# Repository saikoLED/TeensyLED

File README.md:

TeensyLED Controller
====================
Copyright Brian Neltner 2015<br/>
Version 0.4 - May 21, 2015

Summary
-------
This provides a basic library and example code for interacting
with a RGBW LED light using Hue, Saturation, and Intensity (HSI)
mode. Also provided are a basic USB interface example, and an example
for using the fully isolated DMX interface.

CircuitHub design created for this board with pre-identified working
parts. Licensed under CERN Open Hardware license (http://www.ohwr.org/projects/cernohl) which
allows for anyone to copy, modify and distribute this design (and products manufactured therefrom) so long
as they are licensed under identical terms & maintain all copyrights.

https://circuithub.com/projects/neltnerb/TeensyLED

Software Features
-----------------
- HSI to RGBW library for interacting with LED sources with color correction.
- PID based fader that follows a random walk through colorspace.
- Tested basic DMX receiving software (just prints DMX data to USB Serial port for now).
- Basic debug example to set the brightness from the USB port.

For more information about the HSI Colorspace developed by SaikoLED
please check out:
- [Why every LED light should be using HSI colorspace.](http://blog.saikoled.com/post/43693602826/why-every-led-light-should-be-using-hsi)
- [How to convert from HSI to RGB+white.](http://blog.saikoled.com/post/44677718712/how-to-convert-from-hsi-to-rgb-white)
- [Implementing arbitrary color correction with the myki!](http://blog.saikoled.com/post/45630908157/implementing-arbitrary-color-correction-with-the)
- [Talk about HSI Colorspace and RGBW](http://blog.saikoled.com/post/71708131057/talk-about-hsi-colorspace-and-rgbw)

If you are curious about our other projects, you can visit our [blog](http://blog.saikoled.com).

Hardware Features
-----------------

[Schematics and Board Drawings](Eagle Design/TeensyLED.pdf)

- Teensy 3.1 socket.
- RJ45-based DMX Connectors as per DMX-512A.
- Fully isolated DMX-compatible RS485 Interface (ADM2582E).
- Header to switch polarity of DMX signal for compatibility.
- 4x 700mA BJT based current sinks (670-730mA typical).
- Current sinks capable of driving 700mA with 75ns pulse widths.
- 75nm pulse width allows 16-bit PWM at 183Hz, or 8-bit PWM at very fast. 16-bit PWM possible at higher PWM frequencies, but with increased non-linearity for low codes. See Simulations directory for more detail on theoretical performance.
- 5-24VDC board compatibility, with the Vin routed directly to LED V+. Up to 5A allowed by CP-202AH-ND barrel plug connector. Voltage limit is due to barrel plug connector, up to 48VDC can be wired directly using the available test point.
- Built in high efficiency switching regulator to provide 3.7VDC.
- Designed to fit into Hammond 1455C801 Extruded Aluminum Enclosure.
- 8-pin expansion header to access 3.3V, GND, DAC, A0 (SCK), A1/A2 (Touch), and DIN/DOUT (SPI/USART).
- PTC Fuse to prevent damage from shorts or over-power.
- Reverse protection diodes on power inlet and flyback diodes on each LED output to prevent reverse bias.

Hardware Performance
--------------------
Simulations have been done on the current sinking circuitry in order to optimize the response time and stability, and real measurements demonstrate comparable performance. Simulations were done using LTSpice and the vendor supplied model for the ZXT1053AK. These simulations are limited in predicting real performance, particularly in the realm of thermal issues.

###Circuit Model

###Current Output with 1μs pulse.

###Current Output with 100ns pulse.

###Estimated current load from controller pin.

Major Hardware Limitations
--------------------------
- Heat dissipation at the BJTs is the primary limiting factor on maximum power. Switching regulators
are unfortunately inappropriate for such high speed PWM capabilities.
  - Although the BJTs chosen are rated to 4.4W each, at 700mA and a
    typical minimum drop from the top of the BJT to ground of 3V for
    good regulation, power dissipation throughout the board is likely
    to be a bare minimum of 2.1W per channel fully on.
  - I think that if you operate the system in HSI mode, where the
    total current sent to the LEDs is limited to 700mA, split between
    the various channels to change colors, you can probably get away
    with as much as 4W from that subsystem. This is power lost in the
    current sink itself, the power of the LEDs is unimportant.
  - This limits the voltage you can have between the *bottom* of your
    LED chain (no matter how long it is) and ground to under *5VDC*.
  - I am thinking about a new design that will automatically regulate
    down the voltage at the top of the LEDs to the minimum needed
    for reliable regulation based on feedback, but this is a work in
    progress. Perhaps for version 2.0.
- High current and high frequency PWM may radiate excessively for FCC. There is a ferrite bead to improve FCC compatibility, but the wiring between this board and the LEDs will be a significant radiator and must be done with care if the result is intended for sale.
- High current and frequency PWM may degrade ADC measurements, especially from high-
    impedance sources.

License
-------
All software, hardware designs, and hardware design files are licensed
under the GPL.

> TeensyLED Controller is free software and hardware: you can redistribute
> it and/or modify it under the terms of the GNU General Public License
> as published by the Free Software Foundation, either version 3 of the
> License, or (at your option) any later version.
> 
> TeensyLED Controller is distributed in the hope that it will be useful,
> but WITHOUT ANY WARRANTY; without even the implied warranty of
> MERCHANTABILITY or FITNESS FOR A PARTICULAR PURPOSE.  See the
> GNU General Public License for more details.
> 
> You should have received a copy of the GNU General Public License
> along with TeensyLED Controller.  If not, see <http://www.gnu.org/licenses/>.

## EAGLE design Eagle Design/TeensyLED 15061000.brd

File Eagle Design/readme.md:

Board Design files for TeensyLED (EagleCad).

CircuitHub populated design that you may use to produce copies of this board.
https://circuithub.com/projects/neltnerb/TeensyLED

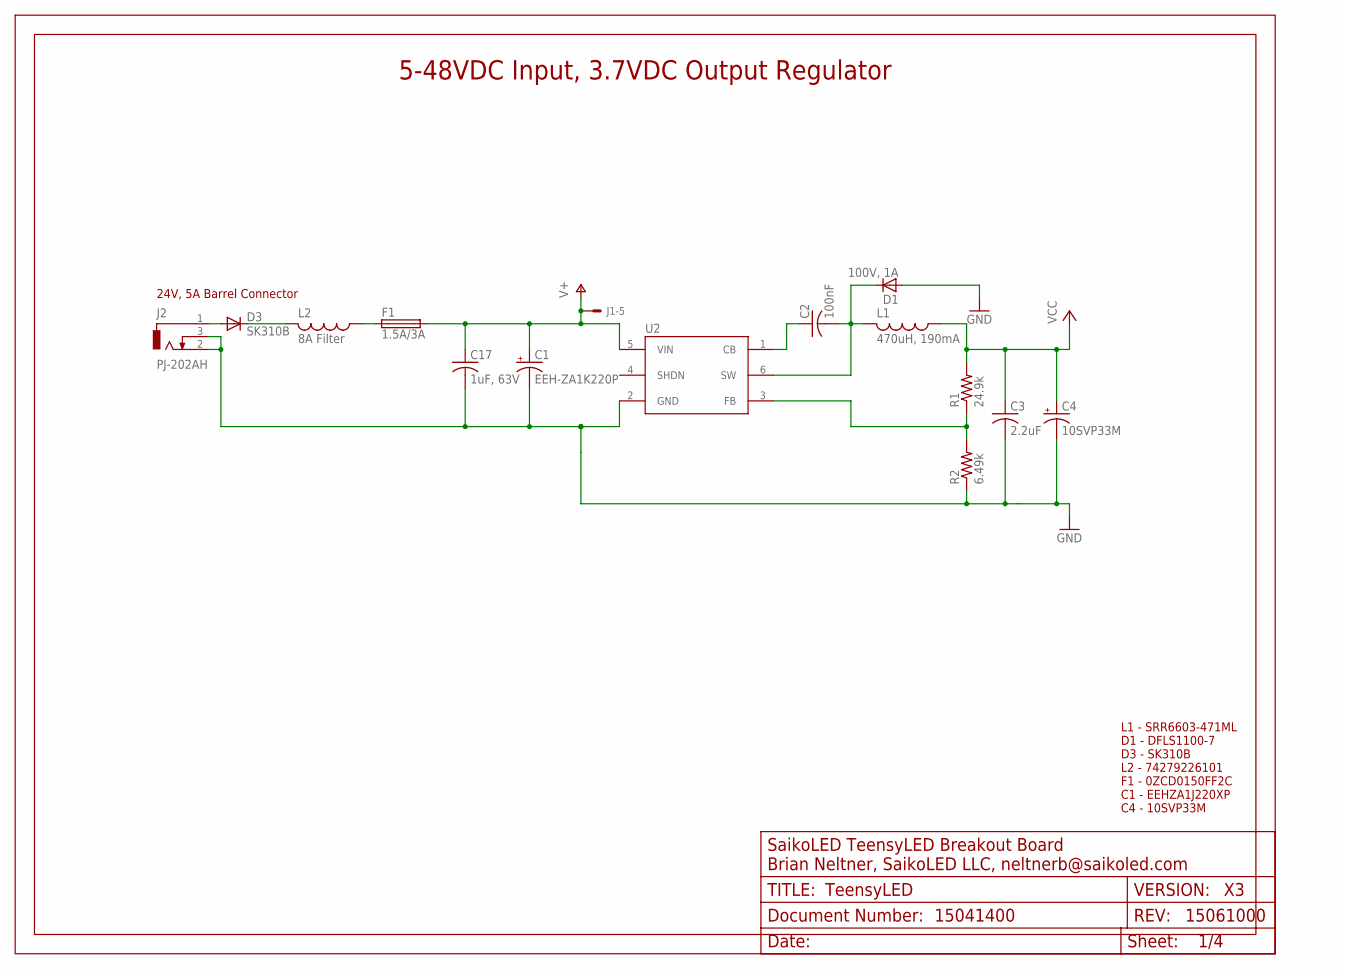
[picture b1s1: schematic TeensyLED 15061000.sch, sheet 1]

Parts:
C1: EEH-ZA1K220P; PANASONIC_F
C2: 100nF; C0805K
C3: 2.2uF; C0402PRO; MPN MCLV4R7M1HB-0513-RH
C4: 10SVP33M; PANASONIC_B
C17: 1uF, 63V; C0805K; MPN MCLV4R7M1HB-0513-RH
D1: 100V, 1A; DFLS1100
D3: SK310B; SMB
F1: 1.5A/3A; 2920
FRAME1: LETTER_LNOSILK; EMPTY
J1: 22-05-7058-05; 7395-05
J2: PJ-202AH
L1: 470uH, 190mA; SRR6603
L2: 8A Filter; L1812
R1: 24.9k; R0402PRO; MPN BLU0402-9762-BT25W
R2: 6.49k; R0402PRO; MPN ERJ-3EKF4123V
U2: LMR16006YDDCT; DDC0006A; MPN MCF 0.25W 1K

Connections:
GND: C1.-, C3.2, C4.-, C17.2, D1.A, J2.2 (3), J2.3 (2), R2.1, U2.2 (GND); also elsewhere on the board
unnamed: C2.1, U2.1 (CB)
unnamed: F1.P$1 (1), L2.1
unnamed: R1.1, R2.2, U2.3 (FB)
unnamed: D3.C, L2.2
unnamed: D3.A, J2.1
V+: C1.+, C17.1, F1.P$2 (2), J1.5, U2.5 (VIN); also elsewhere on the board
VCC: C3.1, C4.+, L1.P$1 (1), R1.2; also elsewhere on the board
VSW: C2.2, D1.C, L1.P$2 (2), U2.6 (SW)

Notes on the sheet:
5-48VDC Input, 3.7VDC Output Regulator
24V, 5A Barrel Connector
L1 - SRR6603-471ML D1 - DFLS1100-7 D3 - SK310B L2 - 74279226101 F1 - 0ZCD0150FF2C C1 - EEHZA1J220XP C4 - 10SVP33M

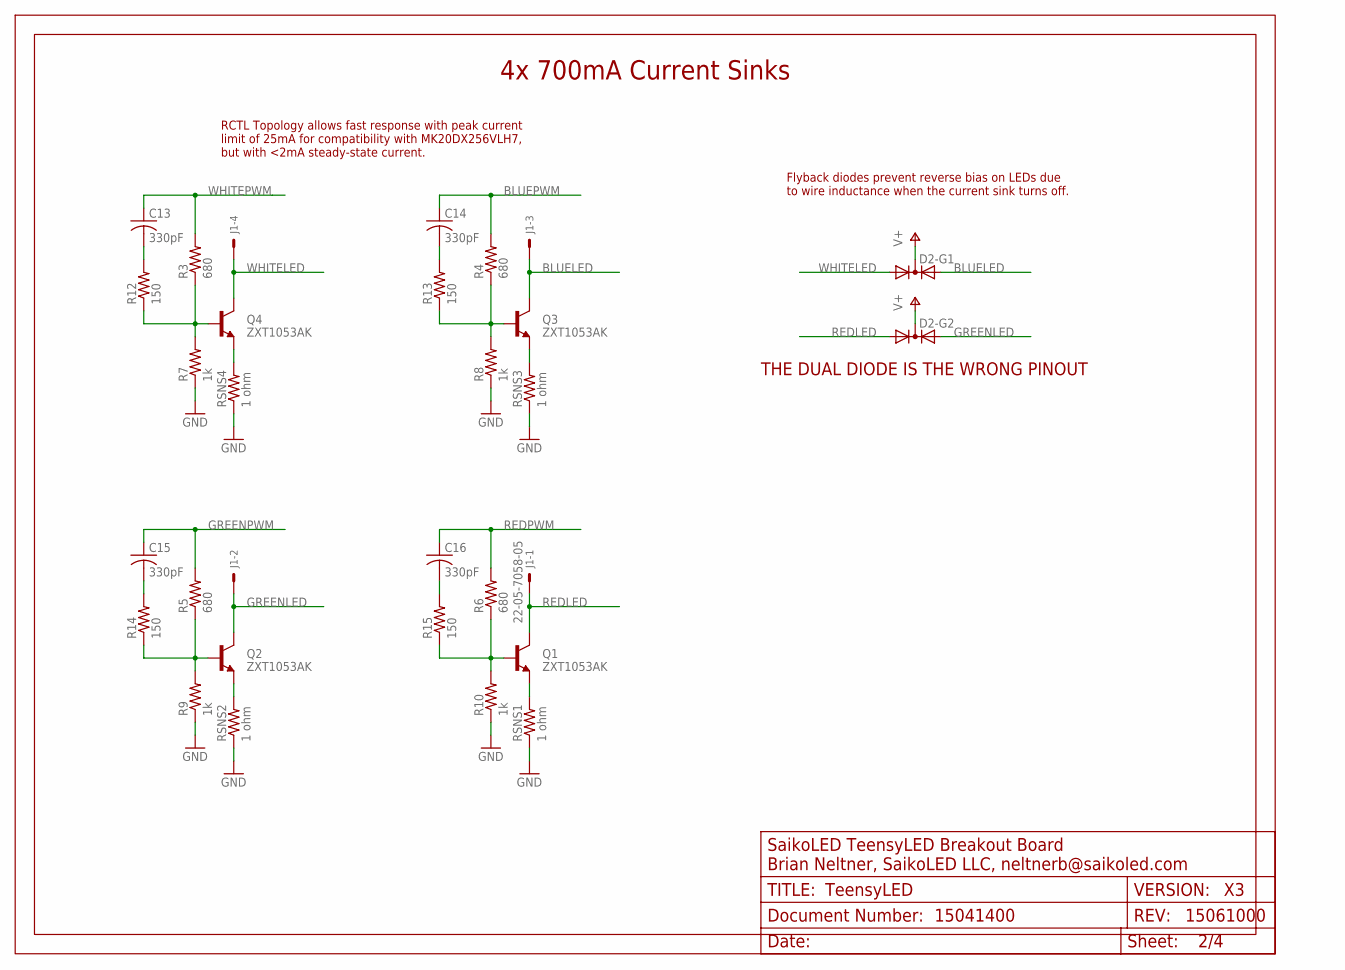
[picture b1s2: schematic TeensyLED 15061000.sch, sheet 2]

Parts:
C13, C14, C15, C16: 330pF; C0402PRO
D2: DUAL_DIODE_AC-CA-SOT363; SOT363_PHILIPS
FRAME2: LETTER_LNOSILK; EMPTY
J1: 22-05-7058-05; 7395-05
Q1, Q2, Q3, Q4: ZXT1053AK; TO252
R3, R4, R5, R6: 680; R0402PRO
R7, R8, R9, R10: 1k; R0402PRO
R12, R13, R14, R15: 150; R0402PRO
RSNS1, RSNS2, RSNS3, RSNS4: 1 ohm; R1206

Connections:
BLUELED: D2.3 (A2), J1.3, Q3.C
BLUEPWM: C14.1, R4.2; also elsewhere on the board
GND: R7.1, R8.1, R9.1, R10.1, RSNS1.1, RSNS2.1, RSNS3.1, RSNS4.1; also elsewhere on the board
GREENLED: D2.4 (A2), J1.2, Q2.C
GREENPWM: C15.1, R5.2; also elsewhere on the board
unnamed: Q2.E, RSNS2.2
unnamed: Q4.E, RSNS4.2
unnamed: Q3.E, RSNS3.2
unnamed: Q1.E, RSNS1.2
unnamed: Q2.B, R5.1, R9.2, R14.1
unnamed: Q4.B, R3.1, R7.2, R12.1
unnamed: Q1.B, R6.1, R10.2, R15.1
unnamed: C13.2, R12.2
unnamed: C14.2, R13.2
unnamed: C15.2, R14.2
unnamed: C16.2, R15.2
R23: Q3.B, R4.1, R8.2, R13.1
REDLED: D2.6 (A1), J1.1, Q1.C
REDPWM: C16.1, R6.2; also elsewhere on the board
V+: D2.2 (K), D2.5 (K); also elsewhere on the board
WHITELED: D2.1 (A1), J1.4, Q4.C
WHITEPWM: C13.1, R3.2; also elsewhere on the board

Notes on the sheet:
4x 700mA Current Sinks
RCTL Topology allows fast response with peak current limit of 25mA for compatibility with MK20DX256VLH7, but with <2mA steady-state current.
Flyback diodes prevent reverse bias on LEDs due to wire inductance when the current sink turns off.
THE DUAL DIODE IS THE WRONG PINOUT

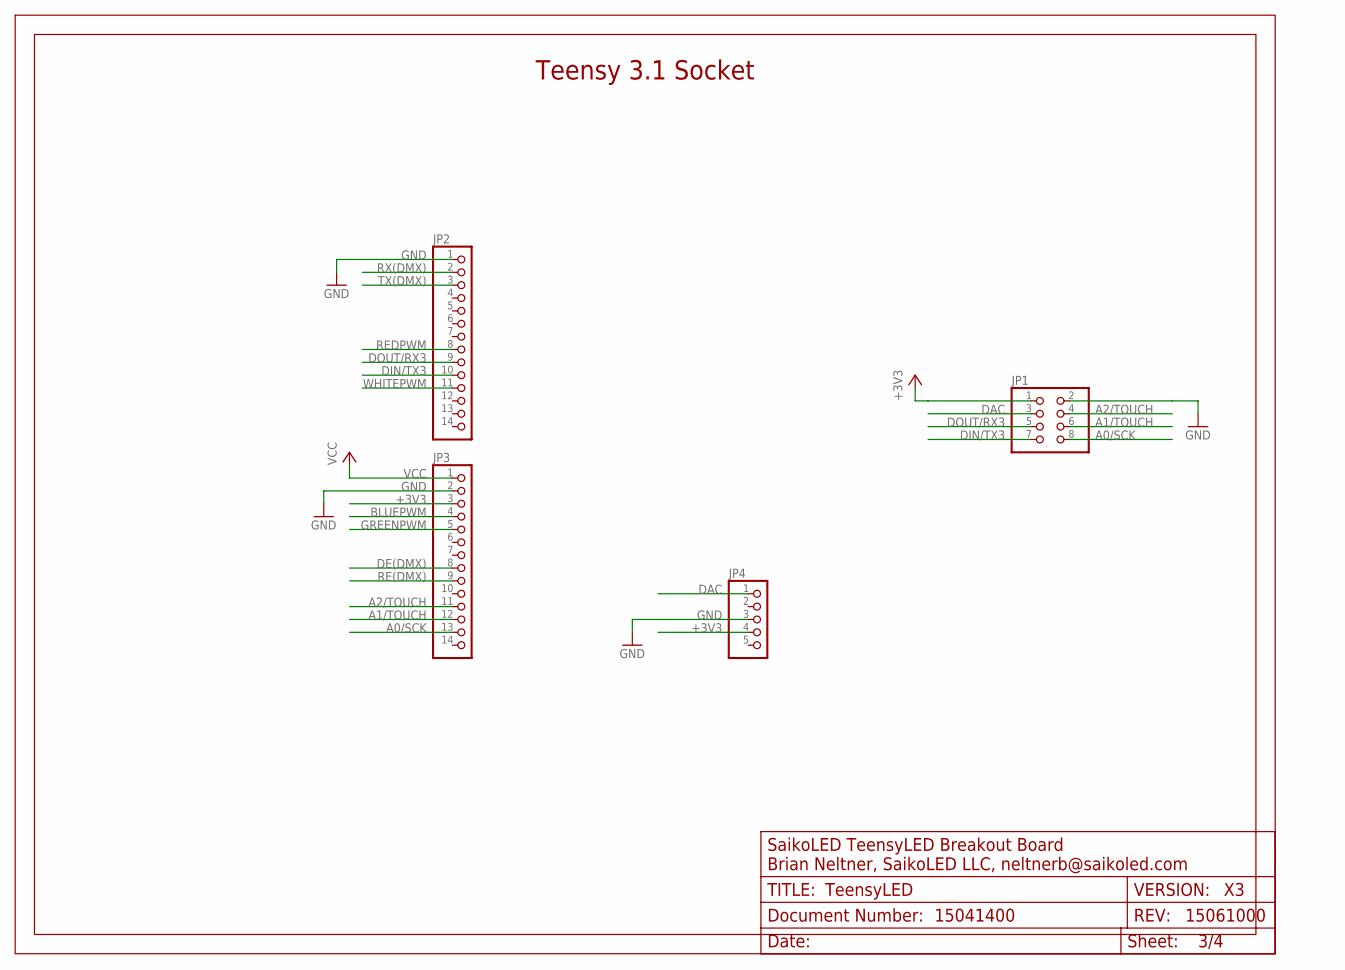
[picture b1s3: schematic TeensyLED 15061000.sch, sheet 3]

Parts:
FRAME3: LETTER_LNOSILK; EMPTY
JP1: PINHD-2X4; 2X04
JP2, JP3: PINHD-1X14/ROUND; 1X14/ROUND
JP4: PINHD-1X5/ROUND; 1X05/ROUND

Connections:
+3V3: JP1.1, JP3.3, JP4.4; also elsewhere on the board
A0/SCK: JP1.8, JP3.13
A1/TOUCH: JP1.6, JP3.12
A2/TOUCH: JP1.4, JP3.11
BLUEPWM: JP3.4; also elsewhere on the board
DAC: JP1.3, JP4.1
DE(DMX): JP3.8; also elsewhere on the board
DIN/TX3: JP1.7, JP2.10
DOUT/RX3: JP1.5, JP2.9
GND: JP1.2, JP2.1, JP3.2, JP4.3; also elsewhere on the board
GREENPWM: JP3.5; also elsewhere on the board
RE(DMX): JP3.9; also elsewhere on the board
REDPWM: JP2.8; also elsewhere on the board
RX(DMX): JP2.2; also elsewhere on the board
TX(DMX): JP2.3; also elsewhere on the board
VCC: JP3.1; also elsewhere on the board
WHITEPWM: JP2.11; also elsewhere on the board

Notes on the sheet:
Teensy 3.1 Socket

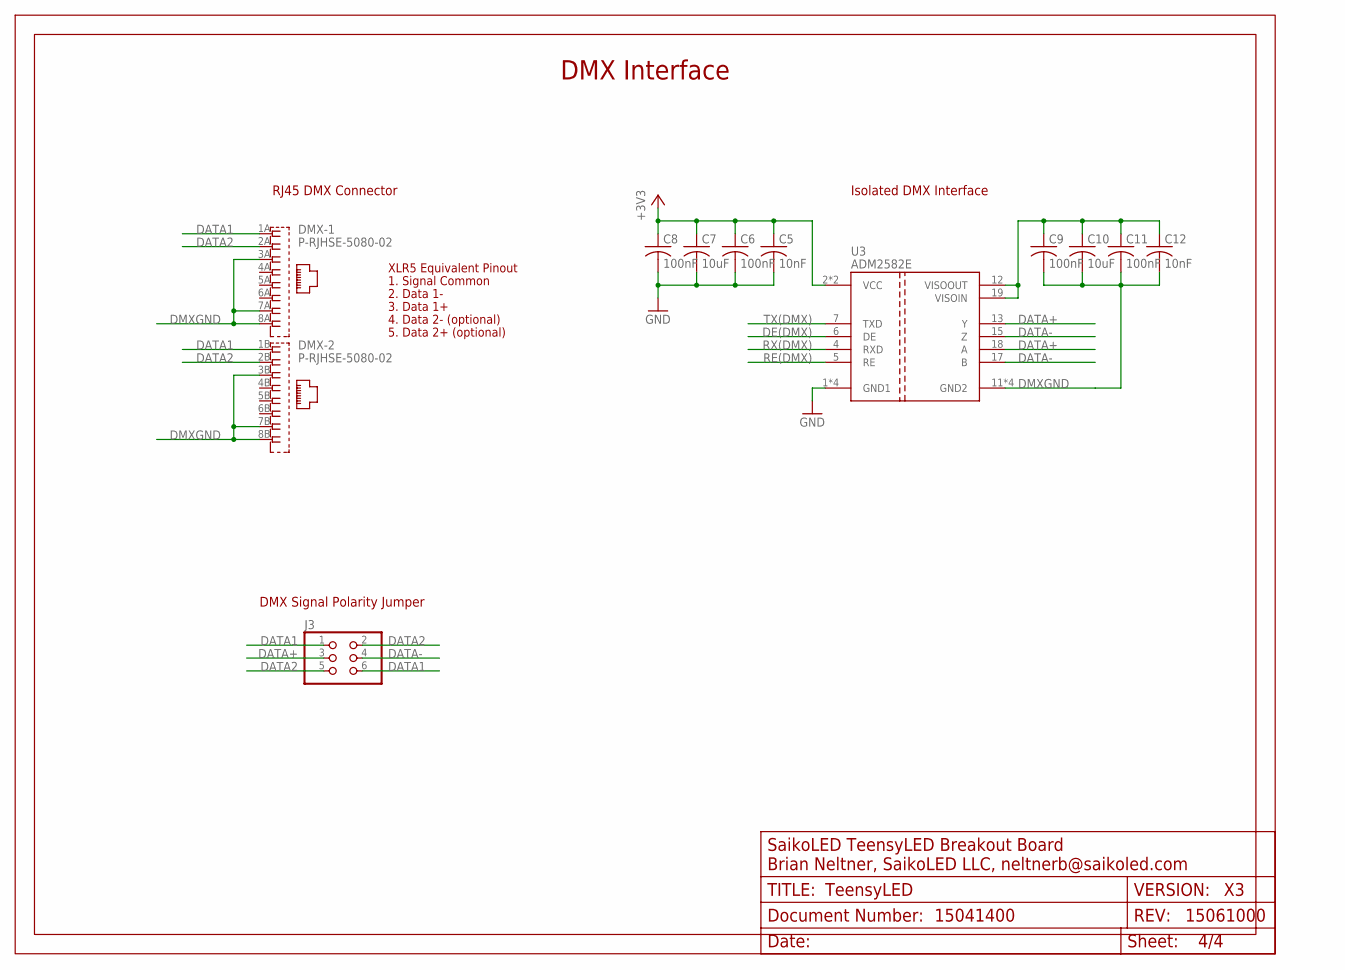
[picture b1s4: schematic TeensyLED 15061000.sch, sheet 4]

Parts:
C5, C12: 10nF; C0402PRO
C6, C8, C9, C11: 100nF; C0402PRO
C7, C10: 10uF; C0402PRO
DMX: P-RJHSE-5080-02
FRAME4: LETTER_LNOSILK; EMPTY
J3: PINHD-2X3; 2X03
U3: ADM2582E; SO-20DW

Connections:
+3V3: C5.1, C6.1, C7.1, C8.1, U3.2 (VCC), U3.8 (VCC); also elsewhere on the board
DATA1: DMX.1A (1), DMX.1B (1), J3.1, J3.6
DATA2: DMX.2A (2), DMX.2B (2), J3.2, J3.5
DATA+: J3.3, U3.13 (Y), U3.18 (A)
DATA-: J3.4, U3.15 (Z), U3.17 (B)
DE(DMX): U3.6 (DE); also elsewhere on the board
DMXGND: C9.2, C10.2, C11.2, C12.2, DMX.3A (3), DMX.3B (3), DMX.7A (7), DMX.7B (7), DMX.8A (8), DMX.8B (8), U3.11 (GND2), U3.14 (GND2), U3.16 (GND2), U3.20 (GND2)
GND: C5.2, C6.2, C7.2, C8.2, U3.1 (GND1), U3.3 (GND1), U3.9 (GND1), U3.10 (GND1); also elsewhere on the board
unnamed: C9.1, C10.1, C11.1, C12.1, U3.12 (VISOOUT), U3.19 (VISOIN)
RE(DMX): U3.5 (RE); also elsewhere on the board
RX(DMX): U3.4 (RXD); also elsewhere on the board
TX(DMX): U3.7 (TXD); also elsewhere on the board

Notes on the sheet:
XLR5 Equivalent Pinout
1. Signal Common
2. Data 1-
3. Data 1+
4. Data 2- (optional)
5. Data 2+ (optional)
Isolated DMX Interface
DMX Signal Polarity Jumper
RJ45 DMX Connector
DMX Interface

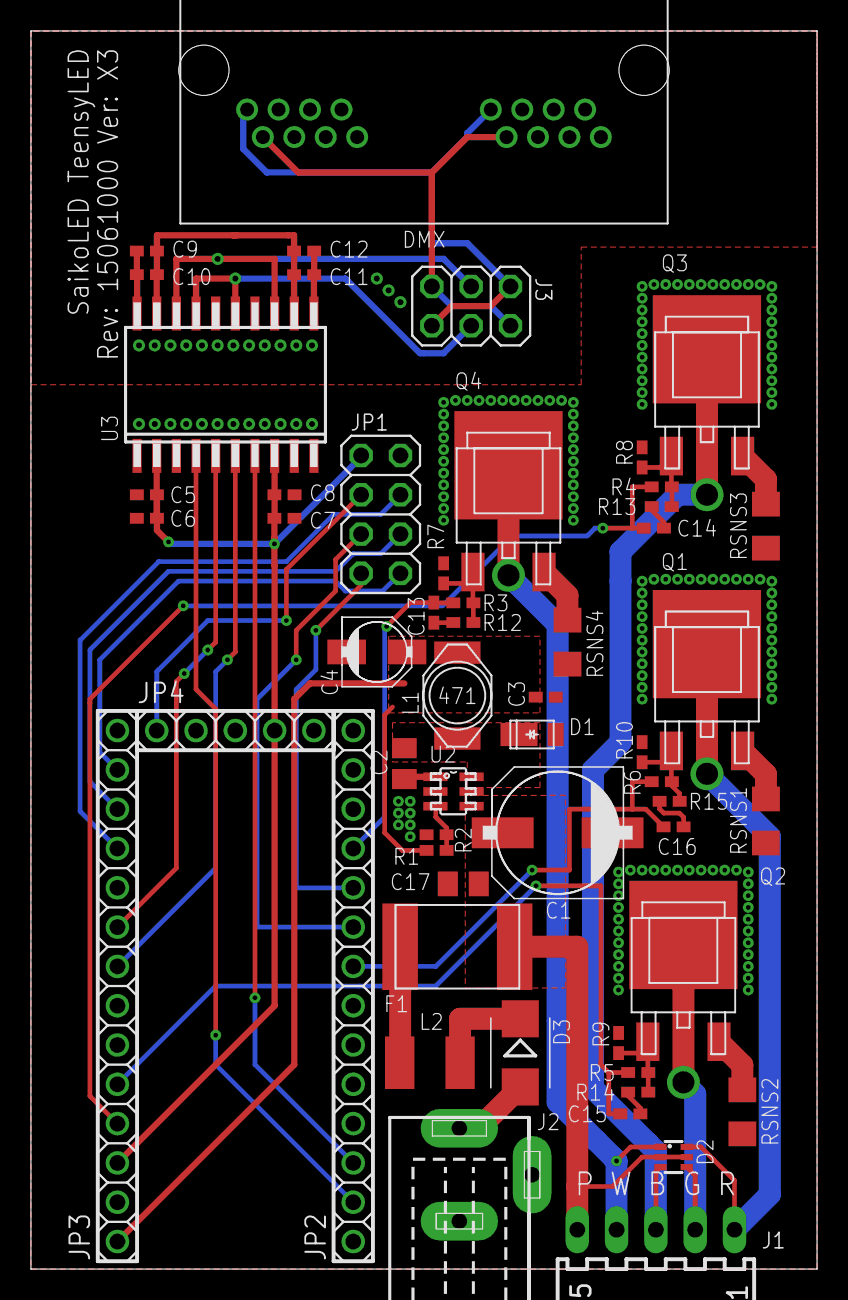
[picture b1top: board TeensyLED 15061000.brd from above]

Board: 2 copper layers, 50.8 x 80.0 mm, 59 parts (0 on the bottom side), 46 nets.

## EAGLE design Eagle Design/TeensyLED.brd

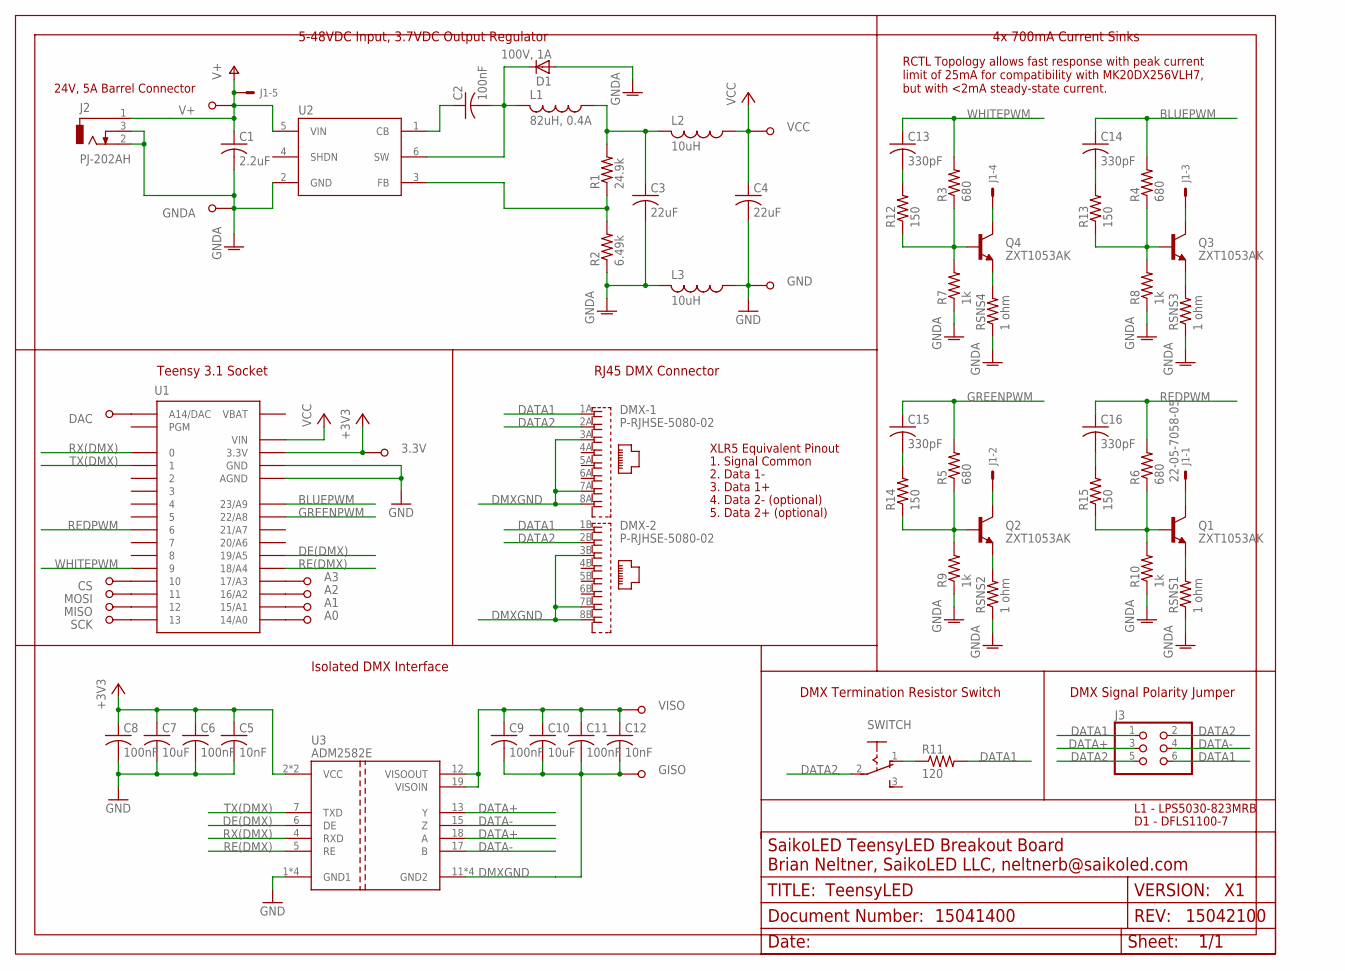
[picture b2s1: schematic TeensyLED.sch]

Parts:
3.3V: TESTPOINT5019; 5019
A0, A1, A2, A3: TESTPOINT5019; 5019
C1: 2.2uF; C1210K
C2: 100nF; C0805K
C3: 22uF; C0805K; MPN MCLV4R7M1HB-0513-RH
C4: 22uF; C0805K
C5, C12: 10nF; C0402PRO
C6, C8, C9, C11: 100nF; C0402PRO
C7, C10: 10uF; C0402PRO
C13, C14, C15, C16: 330pF; C0402PRO
CS: TESTPOINT5019; 5019
D1: 100V, 1A; DFLS1100
DAC: TESTPOINT5019; 5019
DMX: P-RJHSE-5080-02
FRAME1: LETTER_L; PCBINFO
GISO: TESTPOINT5019; 5019
GND: TESTPOINT5019; 5019
GNDA: TESTPOINT5019; 5019
J1: 22-05-7058-05; 7395-05
J2: PJ-202AH
J3: PINHD-2X3; 2X03
L1: 82uH, 0.4A; LPS5030
L2, L3: 10uH; L2012C
MISO: TESTPOINT5019; 5019
MOSI: TESTPOINT5019; 5019
Q1, Q2, Q3, Q4: ZXT1053AK; TO252
R1: 24.9k; R0402PRO; MPN BLU0402-9762-BT25W
R2: 6.49k; R0402PRO; MPN ERJ-3EKF4123V
R3, R4, R5, R6: 680; R0402PRO
R7, R8, R9, R10: 1k; R0402PRO
R11: 120; R0402PRO
R12, R13, R14, R15: 150; R0402PRO
RSNS1, RSNS2, RSNS3, RSNS4: 1 ohm; R1206
SCK: TESTPOINT5019; 5019
SWITCH: M251; SK-12F17-G
U1: TEENSY_3.0_BASIC
U2: LMR16006YDDCT; DDC0006A; MPN MCF 0.25W 1K
U3: ADM2582E; SO-20DW
V+: TESTPOINT5019; 5019
VCC: TESTPOINT5019; 5019
VISO: TESTPOINT5019; 5019

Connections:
+3V3: 3.3V.P$1, C5.1, C6.1, C7.1, C8.1, U1.3.3V, U1.3.3V1 (3.3V), U3.2 (VCC), U3.8 (VCC)
BLUEPWM: C14.1, R4.2, U1.23/A9
DATA1: DMX.1A (1), DMX.1B (1), J3.1, J3.6, R11.2
DATA2: DMX.2A (2), DMX.2B (2), J3.2, J3.5, SWITCH.2
DATA+: J3.3, U3.13 (Y), U3.18 (A)
DATA-: J3.4, U3.15 (Z), U3.17 (B)
DE(DMX): U1.19/A5, U3.6 (DE)
DMXGND: C9.2, C10.2, C11.2, C12.2, DMX.3A (3), DMX.3B (3), DMX.7A (7), DMX.7B (7), DMX.8A (8), DMX.8B (8), GISO.P$1, U3.11 (GND2), U3.14 (GND2), U3.16 (GND2), U3.20 (GND2)
GND: C4.2, C5.2, C6.2, C7.2, C8.2, GND.P$1, L3.1, U1.AGND, U1.GND, U1.GND1 (GND), U3.1 (GND1), U3.3 (GND1), U3.9 (GND1), U3.10 (GND1)
GNDA: C1.2, C3.2, D1.A, GNDA.P$1, J2.2 (3), J2.3 (2), L3.2, R2.1, R7.1, R8.1, R9.1, R10.1, RSNS1.1, RSNS2.1, RSNS3.1, RSNS4.1, U2.2 (GND)
GREENPWM: C15.1, R5.2, U1.22/A8
unnamed: C2.2, D1.C, L1.P$2 (2), U2.6 (SW)
unnamed: C2.1, U2.1 (CB)
unnamed: J1.3, Q3.C
unnamed: DAC.P$1, U1.RESET (A14/DAC)
unnamed: R1.1, R2.2, U2.3 (FB)
unnamed: J1.1, Q1.C
unnamed: J1.2, Q2.C
unnamed: Q2.E, RSNS2.2
unnamed: C3.1, L1.P$1 (1), L2.2, R1.2
unnamed: C9.1, C10.1, C11.1, C12.1, U3.12 (VISOOUT), U3.19 (VISOIN), VISO.P$1
unnamed: Q4.E, RSNS4.2
unnamed: Q3.E, RSNS3.2
unnamed: A0.P$1, U1.14/A0
unnamed: R11.1, SWITCH.1 (O)
unnamed: Q1.E, RSNS1.2
unnamed: Q2.B, R5.1, R9.2, R14.1
unnamed: A1.P$1, U1.15/A1
unnamed: A2.P$1, U1.16/A2
unnamed: A3.P$1, U1.17/A3
unnamed: Q4.B, R3.1, R7.2, R12.1
unnamed: CS.P$1, U1.10
unnamed: Q1.B, R6.1, R10.2, R15.1
unnamed: MOSI.P$1, U1.11
unnamed: MISO.P$1, U1.12
unnamed: SCK.P$1, U1.13
unnamed: C13.2, R12.2
unnamed: C14.2, R13.2
unnamed: C15.2, R14.2
unnamed: C16.2, R15.2
Q4: J1.4, Q4.C
R23: Q3.B, R4.1, R8.2, R13.1
RE(DMX): U1.18/A4, U3.5 (RE)
REDPWM: C16.1, R6.2, U1.6
RX(DMX): U1.0, U3.4 (RXD)
TX(DMX): U1.1, U3.7 (TXD)
V+: C1.1, J1.5, J2.1, U2.5 (VIN), V+.P$1
VBAT: U1.VBAT
VCC: C4.1, L2.1, U1.VIN, VCC.P$1
WHITEPWM: C13.1, R3.2, U1.9

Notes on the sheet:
L1 - LPS5030-823MRB
D1 - DFLS1100-7
XLR5 Equivalent Pinout
1. Signal Common
2. Data 1-
3. Data 1+
4. Data 2- (optional)
5. Data 2+ (optional)
DMX Termination Resistor Switch
Isolated DMX Interface
DMX Signal Polarity Jumper
RJ45 DMX Connector
4x 700mA Current Sinks
Teensy 3.1 Socket
5-48VDC Input, 3.7VDC Output Regulator
RCTL Topology allows fast response with peak current limit of 25mA for compatibility with MK20DX256VLH7, but with <2mA steady-state current.
24V, 5A Barrel Connector

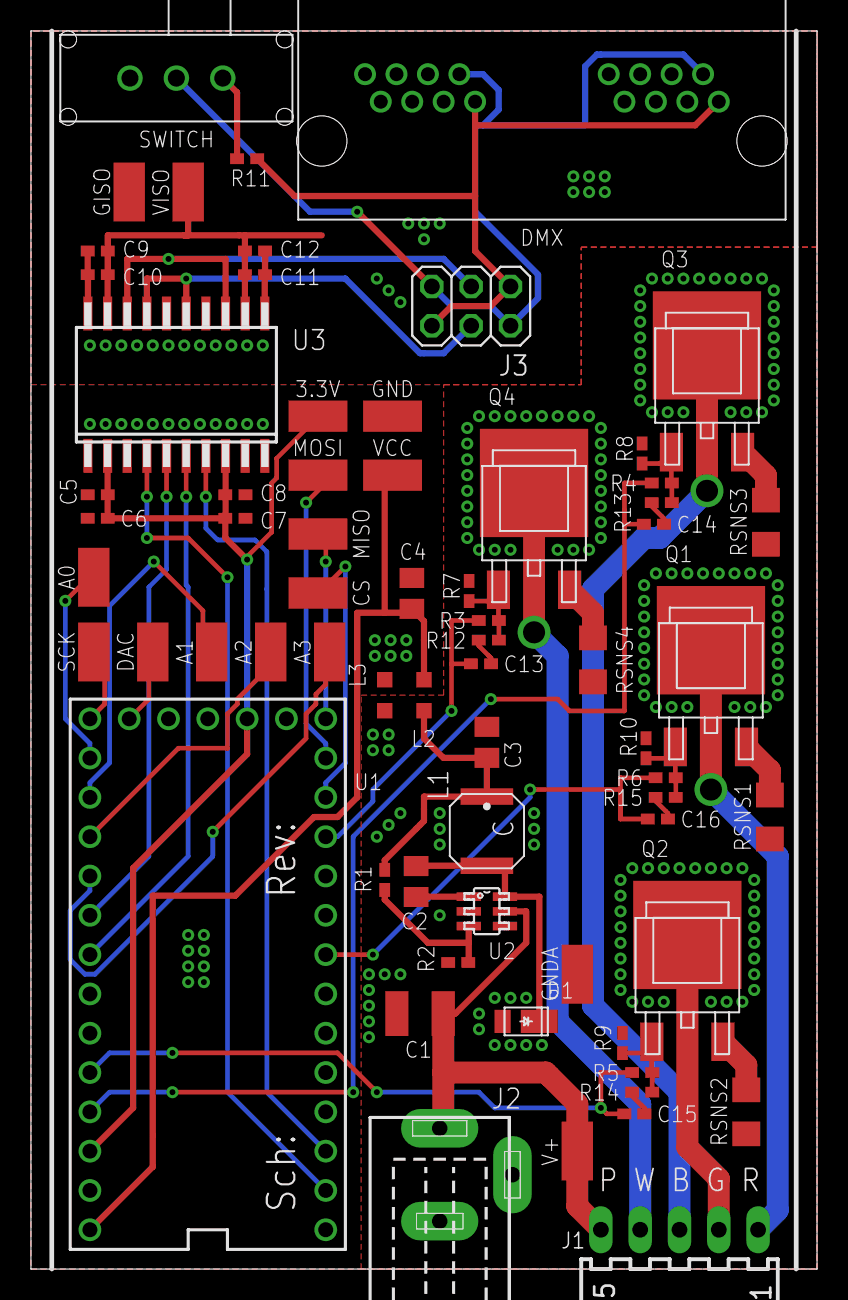
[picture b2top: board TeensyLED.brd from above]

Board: 2 copper layers, 50.8 x 80.0 mm, 68 parts (0 on the bottom side), 49 nets.

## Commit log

2015-04-13 added the starting point code.
2015-04-18 added eagle files.
2015-04-18 updated software to match hardware design, and added basic summary of the project
2015-04-18 changes to summary to use markdown
2015-04-18 added links to references
2015-04-18 fixed typo
2015-04-21 added simulations, updated board design, and updated README.
2015-04-21 cleaned things up, testing readme.md inline images...
2015-04-21 testing images and the like
2015-04-21 fixed typo in image path
2015-04-21 added link to schematic and board pdf file.
2015-04-21 added image of board for display.
2015-04-21 moved image underneath summary
2015-05-20 updated board and new simulations.
2015-05-20 removed old sillyscope scans
2015-05-21 updated board design and project description
2015-11-21 Major Update.
2015-11-21 added CIE colorspace functionality.
2017-06-26 updating license for inclusion in other projects
